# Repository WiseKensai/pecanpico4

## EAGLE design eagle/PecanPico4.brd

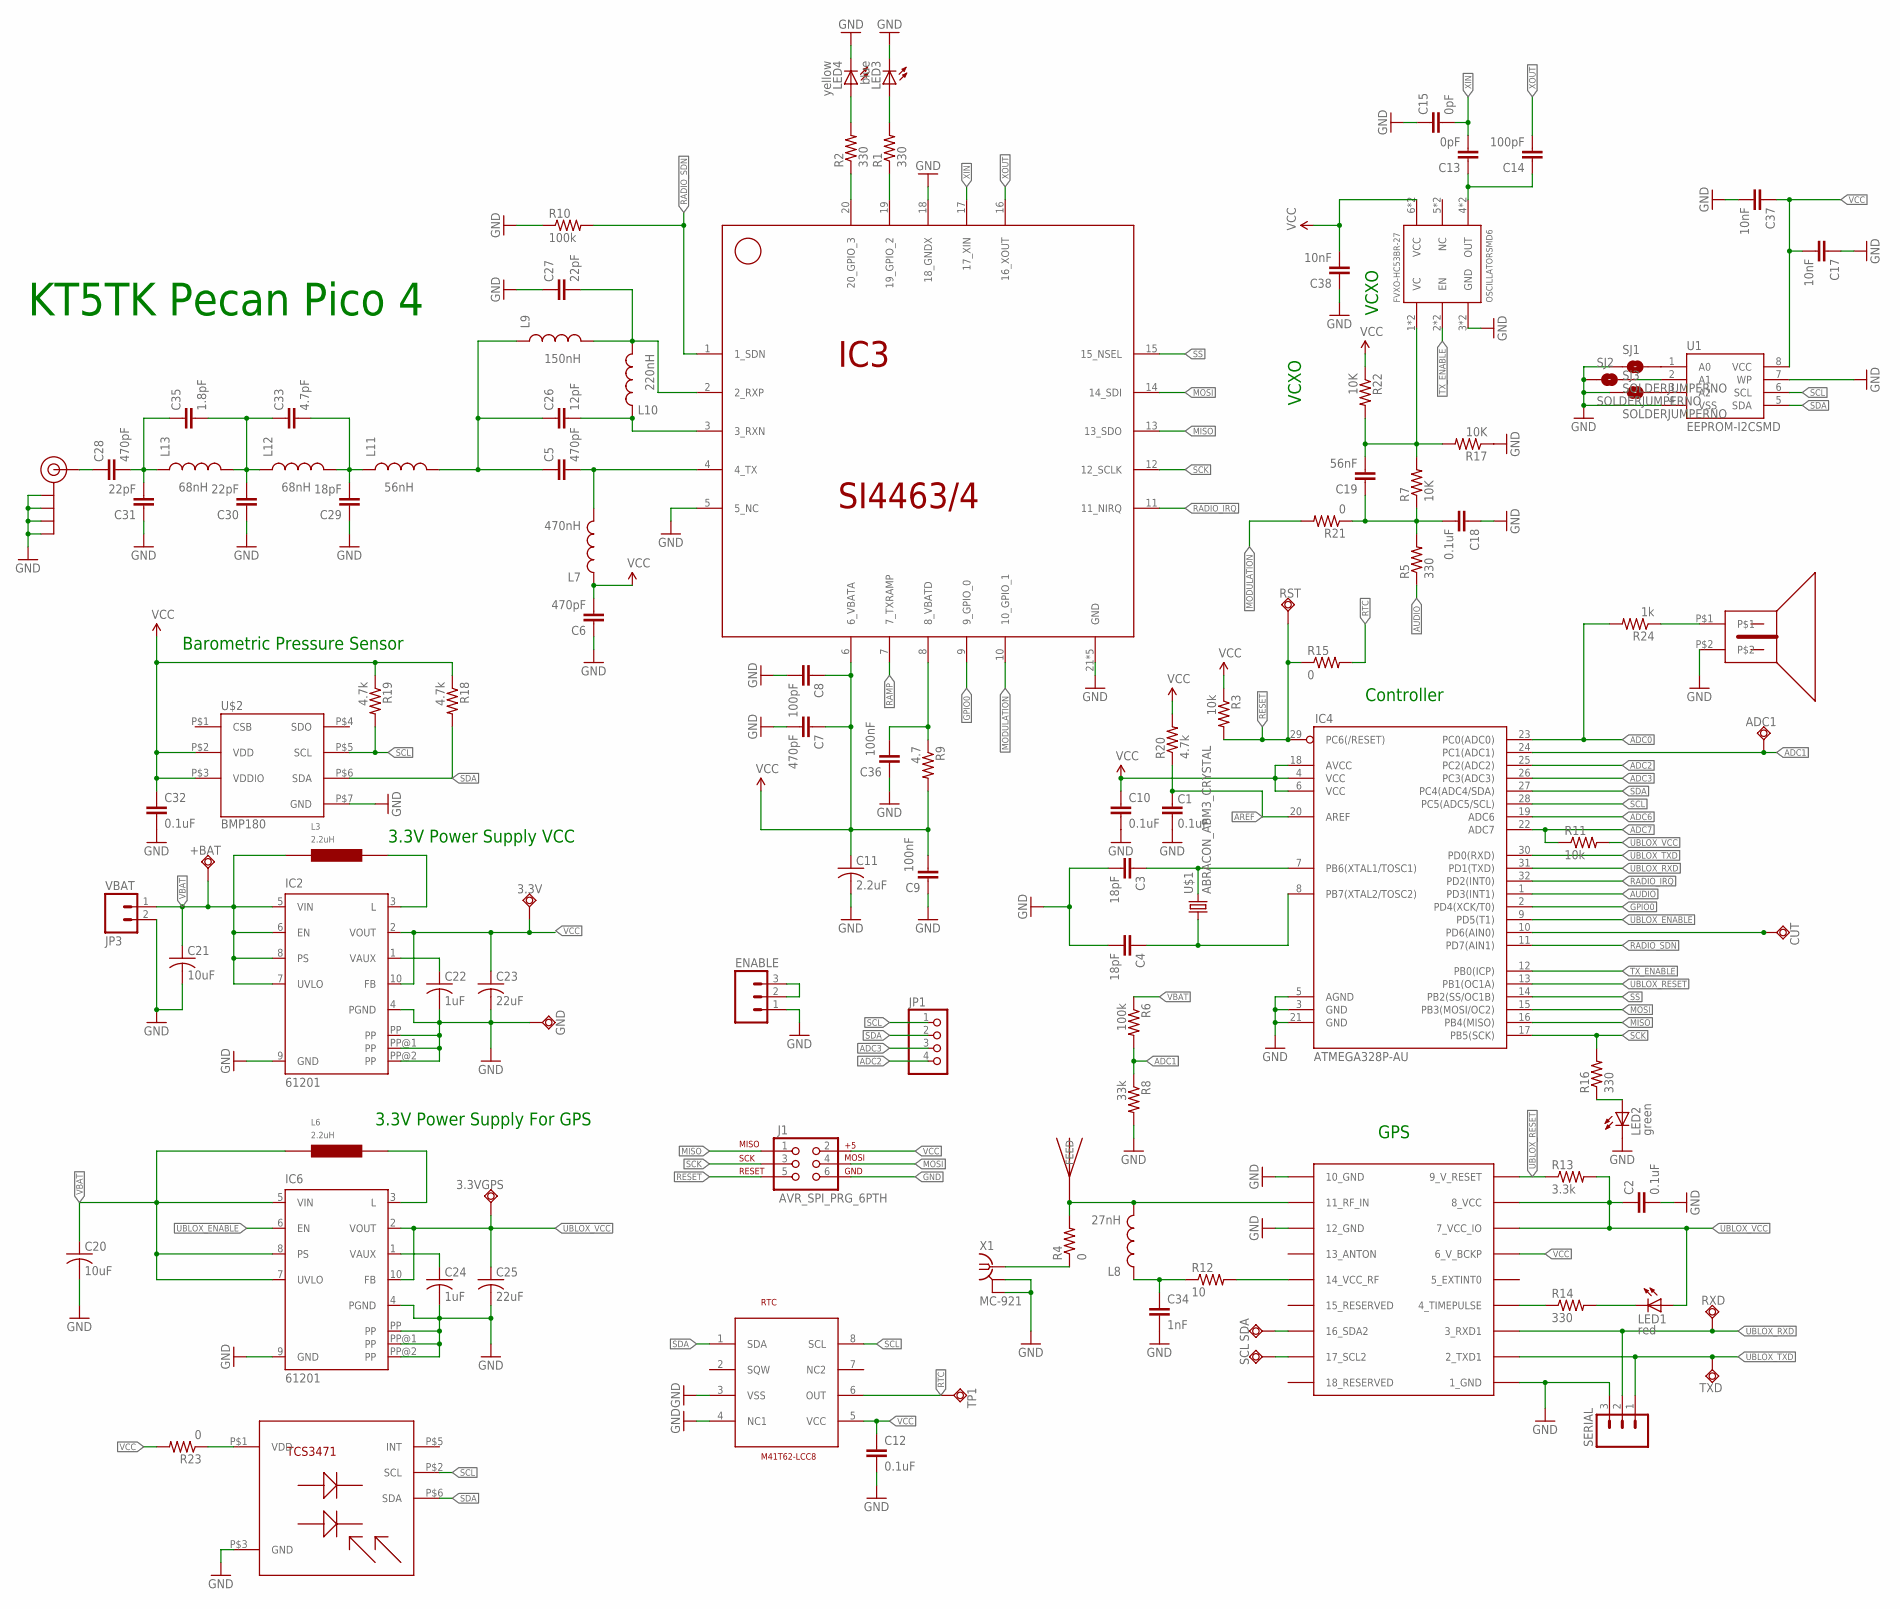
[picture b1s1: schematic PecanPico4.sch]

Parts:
3.3V, 3.3VGPS: TPSQTP06R; TP06R
+BAT: TPSQTP06R; TP06R
ADC1: TPSQTP06R; TP06R
C1, C2, C10, C12, C18, C32: 0.1uF; 0402-CAP
C3, C4, C29: 18pF; 0402-CAP
C5, C6, C7, C28: 470pF; 0402-CAP
C8, C14: 100pF; 0402-CAP
C9, C36: 100nF; 0402-CAP
C11: 2.2uF; C1206
C13, C15: 0pF; 0402-CAP
C17, C37, C38: 10nF; 0402-CAP
C19: 56nF; 0402-CAP
C20, C21: 10uF; C1206
C22, C24: 1uF; C1206
C23, C25: 22uF; C1206
C26: 12pF; 0402-CAP
C27, C30, C31: 22pF; 0402-CAP
C33: 4.7pF; 0402-CAP
C34: 1nF; 0402-CAP
C35: 1.8pF; 0402-CAP
CUT: TPSQTP06R; TP06R
ENABLE: M03PTH; 1X03
FVXO-HC53BR-27: OSCILLATORSMD6; CRYSTAL-SMD-7.5X5.2-6PIN
GND: TPSQTP06R; TP06R
IC2, IC6: 61201; S-PDSO-N10
IC3: SI4463/4; QFN-20
IC4: ATMEGA328P-AU; TQFP32-08
IC5: UBLOX_MAX-6
J1: AVR_SPI_PRG_6PTH; 2X3
J$2: SMA_EDGE; SMA-EDGE
JP1: PINHD-1X4; 1X04
JP3: VBAT; 1X02
L3, L6: 2.2uH; LPS3015
L7: 470nH; 0603
L8: 27nH; 0603
L9: 150nH; 0603
L10: 220nH; 0603
L11: 56nH; 0603
L12, L13: 68nH; 0603
LED1: red; LED-0603
LED2: green; LED-0603
LED3: blue; LED-0603
LED4: yellow; LED-0603
R1, R2, R5, R14, R16: 330; 0402-RES
R3, R11: 10k; 0402-RES
R4, R15, R21, R23: 0; 0402-RES
R6, R10: 100k; 0402-RES
R7, R17, R22: 10K; 0402-RES
R8: 33k; 0402-RES
R9: 4.7; 0402-RES
R12: 10; 0402-RES
R13: 3.3k; 0402-RES
R18, R19, R20: 4.7k; 0402-RES
R24: 1k; 0402-RES
RST: TPSQTP06R; TP06R
RTC: M41T62-LCC8; LCC-8
RXD: TPSQTP06R; TP06R
SCL: TPSQTP06R; TP06R
SDA: TPSQTP06R; TP06R
SERIAL: M03PTH; 1X03
SJ1, SJ2, SJ3: SOLDERJUMPERNO; SJ_2S-NO
SPKR: PKLCS1212E
TCS3471: TCS4371FN; TCS3471FN
TP1: TPSQTP06R; TP06R
TXD: TPSQTP06R; TP06R
U1: EEPROM-I2CSMD; SO08
U$1: ABRACON_ABM3_CRYSTAL
U$2: BMP180; LGA-7
U$3: JTI_ANTENNA-1575AT43A40
X1: MC-921

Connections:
ADC0: IC4.23 (PC0(ADC0)), R24.2
ADC1: ADC1.TP, IC4.24 (PC1(ADC1)), R6.2, R8.1
ADC2: IC4.25 (PC2(ADC2))
ADC3: IC4.26 (PC3(ADC3))
ADC6: IC4.19 (ADC6)
ADC7: IC4.22 (ADC7), R11.1
AREF: C1.2, IC4.20 (AREF), R20.1
AUDIO: IC4.1 (PD3(INT1)), R5.1
CUT: CUT.TP, IC4.10 (PD6(AIN0))
GND: C1.1, C2.2, C3.2, C4.2, C6.1, C7.2, C8.2, C9.1, C10.2, C11.2, C12.2, C15.1, C17.1, C18.1, C20.2, C21.2, C22.2, C23.2, C24.2, C25.2, C27.1, C29.1, C30.1, C31.1, C32.2, C34.2, C36.1, C37.2, C38.1, ENABLE.1, FVXO-HC53BR-27.3 (GND), FVXO-HC53BR-27.3INNER (GND), GND.TP, IC2.4 (PGND), IC2.9 (GND), IC2.PP, IC2.PP@1 (PP), IC2.PP@2 (PP), IC3.5 (5_NC), IC3.18 (18_GNDX), IC3.21 (GND), IC3.22 (GND), IC3.23 (GND), IC3.24 (GND), IC3.25 (GND), IC4.3 (GND), IC4.5 (AGND), IC4.21 (GND), IC5.1_GND, IC5.10_GND, IC5.12_GND, IC6.4 (PGND), IC6.9 (GND), IC6.PP, IC6.PP@1 (PP), IC6.PP@2 (PP), J1.6, J$2.GND@0 (GND), J$2.GND@1 (GND), J$2.GND@2 (GND), J$2.GND@3 (GND), JP3.2, LED2.C, LED3.C, LED4.C, R8.2, R10.1, R17.1, RTC.3 (VSS), RTC.4 (NC1), SERIAL.3, SJ1.1, SJ2.1, SJ3.1, SPKR.P$2, TCS3471.P$3 (GND), U1.4 (VSS), U1.7 (WP), U$2.P$7 (GND), X1.2@1 (GND), X1.2@2 (GND)
GPIO0: IC3.9 (9_GPIO_0), IC4.2 (PD4(XCK/T0))
GPSANT: IC5.11_RF_IN, L8.2, R4.2, U$3.FEED
MISO: IC3.13 (13_SDO), IC4.16 (PB4(MISO)), J1.1
MODULATION: IC3.10 (10_GPIO_1), R21.2
MOSI: IC3.14 (14_SDI), IC4.15 (PB3(MOSI/OC2)), J1.4
unnamed: R23.1, TCS3471.P$1 (VDD)
unnamed: IC5.16_SDA2, SDA.TP
unnamed: IC5.17_SCL2, SCL.TP
unnamed: IC2.3 (L), L3.P$2 (2)
unnamed: IC3.20 (20_GPIO_3), R2.1
unnamed: C18.2, C19.1, R5.2, R7.1, R21.1
unnamed: IC3.19 (19_GPIO_2), R1.1
unnamed: SJ1.2, U1.1 (A0)
unnamed: C3.1, IC4.7 (PB6(XTAL1/TOSC1)), U$1.P$2 (2)
unnamed: C4.1, IC4.8 (PB7(XTAL2/TOSC2)), U$1.P$1 (1)
unnamed: LED4.A, R2.2
unnamed: LED3.A, R1.2
unnamed: C13.1, C14.1, FVXO-HC53BR-27.4 (OUT), FVXO-HC53BR-27.4INNER (OUT)
unnamed: R4.1, X1.1
unnamed: SJ3.2, U1.3 (A2)
unnamed: SJ2.2, U1.2 (A1)
unnamed: R24.1, SPKR.P$1
unnamed: C22.1, IC2.1 (VAUX)
unnamed: IC6.3 (L), L6.P$2 (2)
unnamed: C19.2, FVXO-HC53BR-27.1 (VC), FVXO-HC53BR-27.1INNER (VC), R7.2, R17.2, R22.2
unnamed: C24.1, IC6.1 (VAUX)
unnamed: C5.2, IC3.4 (4_TX), L7.2
unnamed: C28.1, J$2.SIG (SIGNAL)
unnamed: C26.2, IC3.3 (3_RXN), L10.1
unnamed: C27.2, IC3.2 (2_RXP), L9.2, L10.2
unnamed: C5.1, C26.1, L9.1, L11.2
unnamed: C30.2, C33.1, C35.2, L12.1, L13.2
unnamed: ENABLE.2, ENABLE.3
unnamed: IC5.14_VCC_RF, R12.2
unnamed: C34.1, L8.1, R12.1
unnamed: IC5.4_TIMEPULSE, R14.1
unnamed: LED1.C, R14.2
unnamed: C29.2, C33.2, L11.1, L12.2
unnamed: C28.2, C31.2, C35.1, L13.1
unnamed: LED2.A, R16.1
unnamed: C36.2, IC3.8 (8_VBATD), R9.1
RADIO_IRQ: IC3.11 (11_NIRQ), IC4.32 (PD2(INT0))
RADIO_SDN: IC3.1 (1_SDN), IC4.11 (PD7(AIN1)), R10.2
RAMP: IC3.7 (7_TXRAMP)
RESET: IC4.29 (PC6(/RESET)), J1.5, R3.2, R15.1, RST.TP
RTC: R15.2, RTC.6 (OUT), TP1.TP
SCK: IC3.12 (12_SCLK), IC4.17 (PB5(SCK)), J1.3, R16.2
SCL: IC4.28 (PC5(ADC5/SCL)), R19.2, RTC.8 (SCL), TCS3471.P$2 (SCL), U1.6 (SCL), U$2.P$5 (SCL)
SDA: IC4.27 (PC4(ADC4/SDA)), R18.2, RTC.1 (SDA), TCS3471.P$6 (SDA), U1.5 (SDA), U$2.P$6 (SDA)
SS: IC3.15 (15_NSEL), IC4.14 (PB2(SS/OC1B))
TX_ENABLE: FVXO-HC53BR-27.2 (EN), FVXO-HC53BR-27.2INNER (EN), IC4.12 (PB0(ICP))
UBLOX_ENABLE: IC4.9 (PD5(T1)), IC6.6 (EN)
UBLOX_RESET: IC4.13 (PB1(OC1A)), IC5.9_V_RESET, R13.1
UBLOX_RXD: IC4.31 (PD1(TXD)), IC5.3_RXD1, RXD.TP, SERIAL.2
UBLOX_TXD: IC4.30 (PD0(RXD)), IC5.2_TXD1, SERIAL.1, TXD.TP
UBLOX_VCC: 3.3VGPS.TP, C2.1, C25.1, IC5.7_VCC_IO, IC5.8_VCC, IC6.2 (VOUT), IC6.10 (FB), LED1.A, R11.2, R13.2
VBAT: +BAT.TP, C20.1, C21.1, IC2.5 (VIN), IC2.6 (EN), IC2.7 (UVLO), IC2.8 (PS), IC6.5 (VIN), IC6.7 (UVLO), IC6.8 (PS), JP3.1, L3.P$1 (1), L6.P$1 (1), R6.1
VCC: 3.3V.TP, C6.2, C7.1, C8.1, C9.2, C10.1, C11.1, C12.1, C17.2, C23.1, C32.1, C37.1, C38.2, FVXO-HC53BR-27.6 (VCC), FVXO-HC53BR-27.6INNER (VCC), IC2.2 (VOUT), IC2.10 (FB), IC3.6 (6_VBATA), IC4.4 (VCC), IC4.6 (VCC), IC4.18 (AVCC), IC5.6_V_BCKP, J1.2, L7.1, R3.1, R9.2, R18.1, R19.1, R20.2, R22.1, R23.2, RTC.5 (VCC), U1.8 (VCC), U$2.P$2 (VDD), U$2.P$3 (VDDIO)
XIN: C13.2, C15.2, IC3.17 (17_XIN)
XOUT: C14.2, IC3.16 (16_XOUT)

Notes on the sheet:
KT5TK Pecan Pico 4
Barometric Pressure Sensor
Controller
3.3V Power Supply VCC
3.3V Power Supply For GPS
VCXO
GPS

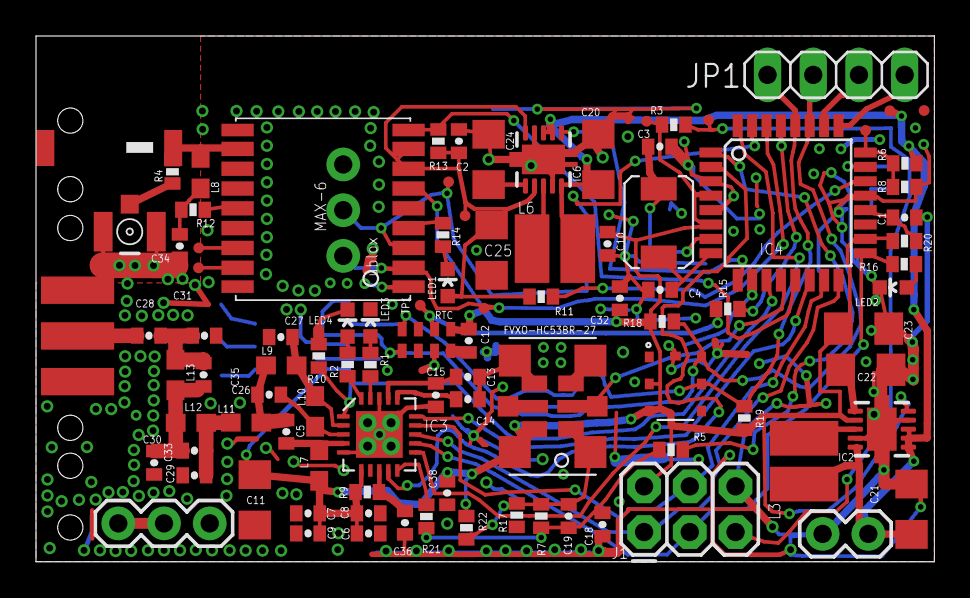
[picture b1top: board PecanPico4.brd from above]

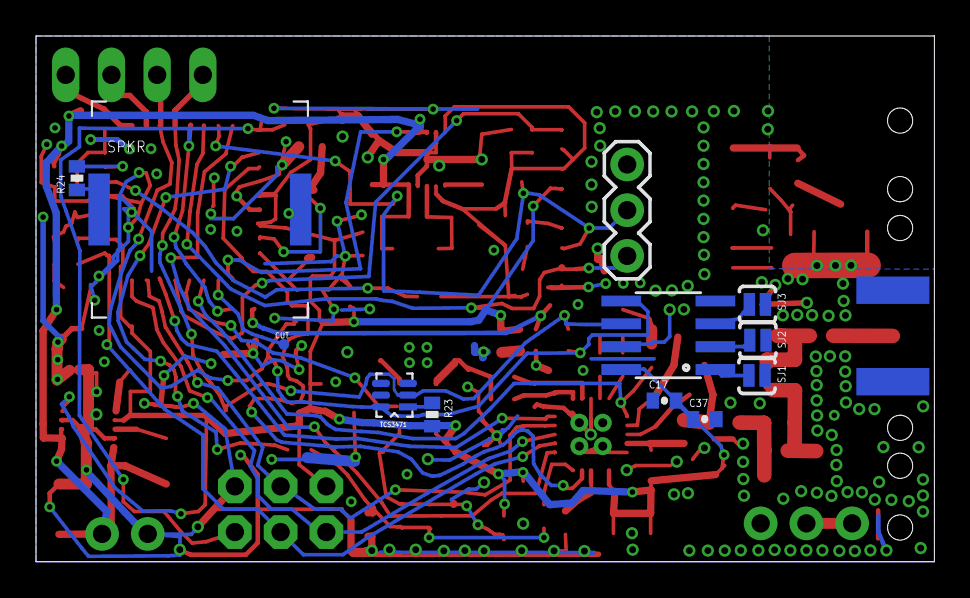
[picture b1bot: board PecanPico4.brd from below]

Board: 2 copper layers, 49.9 x 29.2 mm, 109 parts (12 on the bottom side), 66 nets.

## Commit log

2013-11-12 Added breakout for I2C, ADC2/3
2013-11-12 W2CXM Customizations
    Converted to W2CXM callsign, "Ursine Pico 1" name, and Mike Wozowski
    logo.
2013-11-13 Revised name customizations
    Name change to "Ursus Maximus 1"
2013-11-13 Added Docs and Notes folder, email addy.
    Starting to document the Gerber Layers. Added email address to
    Soldermask.
2013-11-14 Updated the gerber layers doc.
2013-11-14 Guess at gerber layers
2013-11-14 Added Gerber export Job File
2013-11-14 First Gerber Build
2013-11-14 New gerbers, updated job file
2013-11-14 Updated zip file
2013-11-14 Added a "Board Outline" file
    So that "oshpark.com" likes the board.
2013-11-15 Corrected name _ Ursus MINIMUS.
    Doh
2013-11-28 CWBEACON mods
    Beginning mods to beacon CW on a simplex frequency in between APRS
    transmissions.
2013-12-21 i2c changes

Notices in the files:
parts and their libraries:
SparkFun-FreqCtrl_TK: Licensing: CC v3.0 Share-Alike You are welcome to use this library for commercial purposes.
